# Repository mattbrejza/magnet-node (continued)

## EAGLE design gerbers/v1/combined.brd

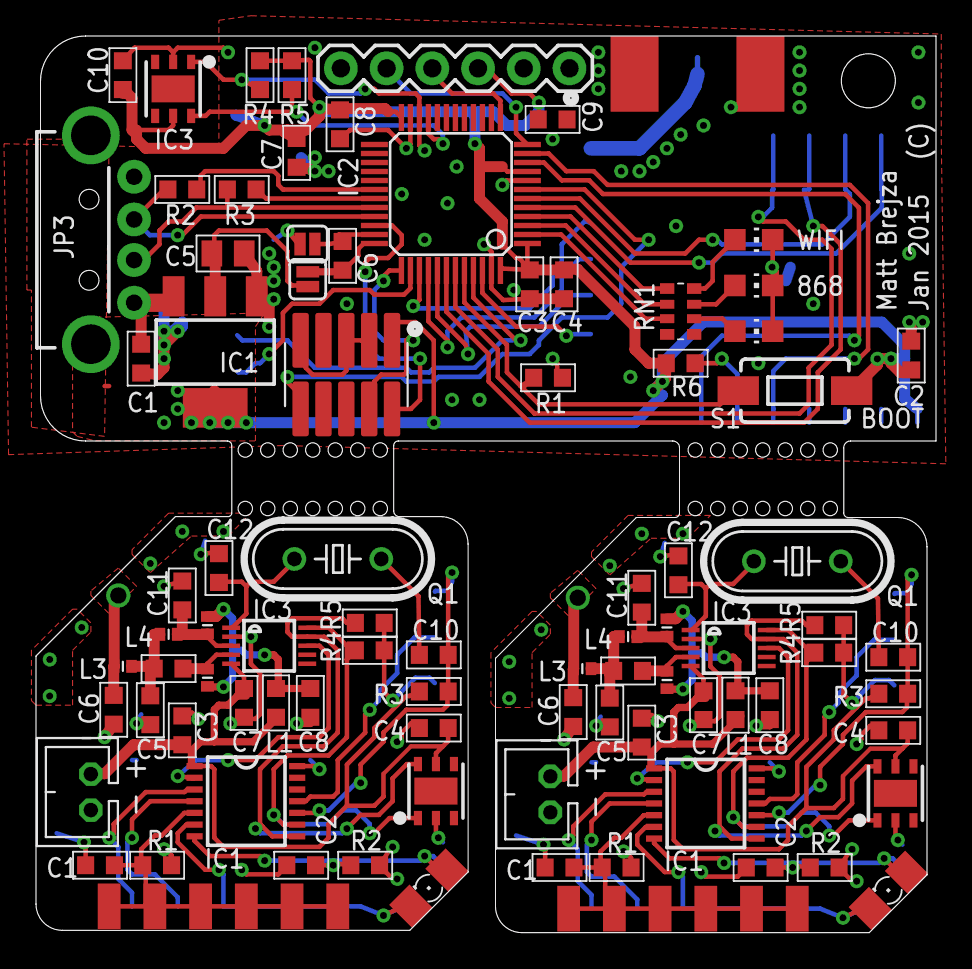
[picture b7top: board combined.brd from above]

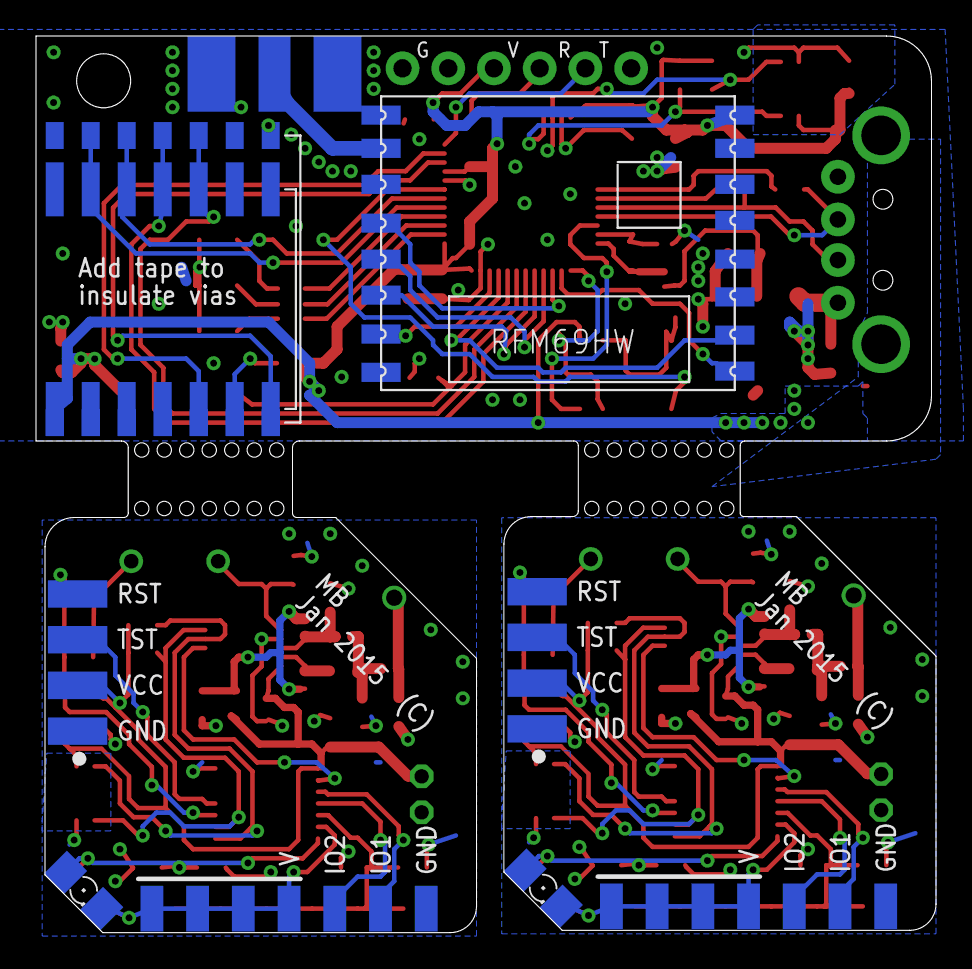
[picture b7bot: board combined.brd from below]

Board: 2 copper layers, 50.0 x 49.8 mm, 97 parts (10 on the bottom side), 76 nets.

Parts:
C1, C2, C3, C13, C22, C23, C26, C27, C28, C29: 100n; C0603-N
C4, C24: C0603-N
C5, C6, C19, C20: 5.1p; C0603-N
C7, C14, C25, C32, C33, C34: 1u; C0603-N
C8, C11, C16, C17: 2.4p; C0603-N
C9, C18: 1.2p; C0603-N
C10, C21: 47n; C0603-N
C12, C15: 14p; C0603-N
C30: 4u7; C0603-N
C31: 4u7; C0805-N
IC1, IC4: MSP430G2X21; TSSOP14
IC2, IC6, IC9: HTU21D; DFN6-L
IC3, IC5: SI4012; MSOP10
IC7: STM32F072; TQFP48
IC8: 1117EMP; SOT223
J1, J2: JST-2-TH
J3: SWD_SHROUD_SMD; SWD_SMD_SHROUD
JP1, JP2: SJ_2S
JP3: USB-A-H
JP4: FTDI_BASICPTH; FTDI_BASIC
L1, L10: 120n; L0603-N
L2, L5, L8, L9: 3.6n; L0402-N
L3, L7: 6.8n; L0402-N
L4, L6: 30n; L0402-N
LED1, LED2, LED3, LED4: 1206
LED5, LED6, LED7: CHIP-LED0805
Q1, Q2: HC49/S
R1, R7: 47k; R0603-N
R2, R6: 1M; R0603-N
R3, R8: 22k; R0603-N
R4, R5, R9, R10, R14, R15: 4k7; R0603-N
R11, R13: 10k; R0603-N
R12: 100k; R0603-N
R16: 1k; R0603-N
RN1: 330; EXB38V
S1: SWITCH-MOMENTARY-2SMD-1101NE; TACTILE-SWITCH-1101NE
SV1, SV3: EDGE_4
SV2, SV4: MA07-1-SMD
U$1, U$2: MA06-1; MA06-1-SMD
U$3: RFM69HW; RFM
U$4: ESP-07
X1: ESP-03
X2: SMA-142-0711-821/826; J502-ND-142-0711-821/826

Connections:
+3V1: C13.1, C14.1, C24.1, IC4.1, IC5.5, IC6.5, J2.1, L10.2, R8.2, R9.2, R10.2, SV1.2
+3V2: C25.1, C27.1, C28.1, C29.1, C31.1, C32.1, C33.1, C34.1, IC7.1, IC7.9, IC7.24, IC7.48, IC8.2, IC8.4, IC9.5, J3.1, JP1.2, JP4.VCC, R14.2, R15.2, R16.1, S1.2, U$3.VCC, U$4.1, X1.1
+3V3: C3.1, C4.1, C7.1, IC1.1, IC2.5, IC3.5, J1.1, L1.2, R3.2, R4.2, R5.2, SV3.2
CH_PD: IC7.5, U$4.13, X1.13
DIO0: IC7.45, U$3.DIO0
DM: IC7.32, JP3.D-, R12.2
DP: IC7.33, JP3.D+, R13.2
GND: C1.1, C2.1, C3.2, C4.2, C5.1, C6.2, C7.2, C8.1, C10.1, C11.1, C12.1, IC1.14, IC2.2, IC3.2, J1.2, Q1.1, R1.1, R2.1, SV2.7, SV3.1
GND1: C13.2, C14.2, C15.1, C16.1, C17.1, C19.1, C20.2, C21.1, C22.1, C23.1, C24.2, IC4.14, IC5.2, IC6.2, J2.2, Q2.1, R6.1, R7.1, SV1.1, SV4.7
GND2: C25.2, C27.2, C28.2, C29.2, C30.2, C31.2, C32.2, C33.2, C34.2, IC7.8, IC7.23, IC7.47, IC8.1, IC9.2, J3.3, J3.5, J3.9, JP2.1, JP3.GND, JP4.GND, LED5.C, LED6.C, LED7.C, R11.1, U$3.GNDA, U$3.GNDB, U$4.8, X1.8, X2.G@1, X2.G@2, X2.G@3, X2.G@4
GPIO0: IC7.10, U$4.7, X1.7
GPIO15: IC7.11, U$4.5, X1.5
I2C2_SCL: IC7.21, IC9.6, R14.1
I2C2_SDA: IC7.22, IC9.1, R15.1
IO1: IC1.3, SV2.6
IO2: IC1.4, SV2.5
IO3: IC4.3, SV4.6
IO4: IC4.4, SV4.5
MISO: IC7.40, U$3.MISO
MOSI: IC7.41, U$3.MOSI
unnamed: IC1.2, IC3.8
unnamed: IC1.11, SV3.3
unnamed: C8.2, L1.1, L2.2, L5.2
unnamed: C12.2, IC3.1, Q1.2
unnamed: IC4.11, SV1.3
unnamed: C5.2, C9.1, L3.1, L4.2
unnamed: C11.2, IC3.3, L4.1, L5.1
unnamed: C9.2, IC3.4, L2.1
unnamed: C6.1, L3.2
unnamed: C15.2, IC5.1, Q2.2
unnamed: C1.2, IC1.5, R1.2, U$1.1, U$1.2, U$1.3, U$1.4, U$1.5, U$1.6
unnamed: C2.2, IC1.7, LED1.A, LED2.A, R2.2
unnamed: C16.2, L8.2, L9.2, L10.1
unnamed: C10.2, IC1.10, R3.1, SV3.4
unnamed: C18.1, C19.2, L6.2, L7.1
unnamed: C17.2, IC5.3, L6.1, L9.1
unnamed: C18.2, IC5.4, L8.1
unnamed: C20.1, L7.2
unnamed: C22.2, IC4.5, R7.2, U$2.1, U$2.2, U$2.3, U$2.4, U$2.5, U$2.6
unnamed: C23.2, IC4.7, LED3.A, LED4.A, R6.2
unnamed: C21.2, IC4.10, R8.1, SV1.4
unnamed: IC4.2, IC5.8
unnamed: C26.1, IC7.36, JP1.1
unnamed: C26.2, IC7.35, JP2.2
unnamed: IC7.44, R11.2, S1.1
unnamed: IC7.31, R12.1
unnamed: IC7.30, R13.1
unnamed: LED5.A, RN1.8
unnamed: LED6.A, RN1.7
unnamed: LED7.A, RN1.6
unnamed: IC7.2, RN1.3
unnamed: IC7.3, RN1.2
unnamed: IC7.4, RN1.1
unnamed: U$3.ANT, X2.1
unnamed: R16.2, U$4.6, X1.6
unnamed: U$4.2, X1.2
unnamed: U$4.4, X1.4
unnamed: U$4.3, X1.3
NRST: IC7.7, J3.10
NSS: IC7.46, U$3.NSS
RST: IC7.38, U$3.RESET
SCK: IC7.39, U$3.SCK
SCL: IC1.8, IC2.6, IC3.9, R5.1
SCL1: IC4.8, IC5.9, IC6.6, R10.1
SDA: IC1.9, IC2.1, IC3.10, R4.1
SDA1: IC4.9, IC5.10, IC6.1, R9.1
SWCLK: IC7.37, J3.4
SWDAT: IC7.34, J3.2
USART1_RX: IC7.43, U$4.10, X1.10
USART1_TX: IC7.42, U$4.11, X1.11
USART2_RX: IC7.13, JP4.TXO
USART2_TX: IC7.12, JP4.RXI
VBUS: C30.1, IC8.3, JP3.VBUS
VCCS: IC1.6, LED1.C, LED2.C, SV2.1, SV2.2, SV2.3, SV2.4
VCCS1: IC4.6, LED3.C, LED4.C, SV4.1, SV4.2, SV4.3, SV4.4
W_RST: IC7.6, U$4.12, X1.12

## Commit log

2014-11-13 started pcb
2014-11-14 initial route
2014-11-14 changing sensor power arragment
2014-11-22 started wifi basestatin
2014-11-23 some routing
2014-11-23 added temp/humid sensor
2014-11-24 moved to smd esp
2014-11-24 something changed probably
2014-11-25 routing improved
2014-11-25 started mppt modelling
2014-11-25 tiding
2014-11-26 started solar node
2014-11-27 added switcher to simulation
2014-12-01 pretty much done
2014-12-01 connector labelljng
2014-12-02 increasing cap package size
2014-12-02 with updated switching stuff
2014-12-08 changed footprints in magnet node
2014-12-18 adding some values and labels
2014-12-18 small changes
2015-01-03 almost done
2015-01-03 routed RST
2015-01-04 removed power control from dht
2015-01-04 almost ready to do
2015-01-05 sent off
2015-01-24 minor changes (i hope)
2015-02-17 adding stencil and couple of values
2015-04-12 started node firmware
2015-04-12 fixing value
2015-04-12 started basestation code
2015-04-12 more basestation tuff
2015-04-12 another file
2015-04-14 added checksum
2015-04-18 adding new breakout
2015-04-20 minor changes
2015-04-27 minor
2015-05-10 minor change
2015-05-30 initial commit of working wifi uplink
2015-05-31 lowered power usage
2015-05-31 wifi fixes
2015-06-22 started wind shield
2015-06-23 turned into assembly
2015-06-24 more 3d stuff
2015-06-30 ui on basestation, adc temp on node
2015-06-30 fixing temp < 0
2015-06-30 can now change wifi network
2015-07-01 improved ui, half way through making wifi nonblocking
2015-07-12 esp stuff is now non blocking
2015-08-07 done some stuff...
2015-08-08 doesnt connect if invalid ssid on startup
2015-08-08 Restructured to include locm3 locally
2015-08-08 Tidying up @mattbrejza's code
2015-08-08 Ignore dependency lists
2015-08-08 Removing shadowed variables and use newlib's _sbrk etc
2015-08-08 More tidying
2015-08-08 removed old locm3
2015-08-08 removed old locm3 mod
2015-08-08 removed old locm3 mod and dir
2015-08-08 Updated locm3 to BuFran's de26102ff6fb5e80afbbc72e0a058746b8cb2272
2015-08-08 Old USB stuff for f0x2
2015-08-08 Working USB roughly, although sometimes fails to enumerate and usbd_poll() isn't run often enough
2015-08-08 Removed a usb write that causes hardfaults
2015-08-10 adding tssop versopn
2015-08-10 some #defines
2015-08-20 Testing a ChibiOS version of the firmware
2015-08-20 getting closer to easy esp programming
2015-08-20 Tidied up board.h to remove artifacts from demo-board-example
2015-08-20 now can flash thru stm32
2015-08-20 Use 'pt boot' or 'pt norm' to enter bootloader or normal passthrough modes on the ESP
2015-08-21 Separated out shell USB stuff
2015-08-21 serusbcfg is not const
2015-08-21 added functionality to allow other threads to get a SDU pointer, so they can chprintf
2015-08-21 typo in comment
2015-08-21 slightly smaller wa is ok for usbserial (for now)
2015-08-21 add semihosting support to allow printf over debug interface
2015-08-22 optionally enable stdio over gdb session
2015-08-23 added light sensor
2015-08-27 some work on the esp
2015-09-01 Updated to ESP thread message format
2015-09-02 RTFM! Objects in mempools must be 32 bit aligned (on stm32)
2015-09-03 working on sending and getting a message from the esp
2015-09-03 Flushes buffers after waiting for the ESP to transmit its stuff after boot
2015-09-03 Once we have a message, process it with all haste!
2015-09-03 We can sleep a little more if the buffer is empty
2015-10-24 reverted to linear buffer
2015-10-24 determining if terminal is attached ???
2015-10-24 receiving and parsing ESP version
2015-10-24 updated chibi
2015-10-24 Working esp version printing over usbser
2015-10-24 Adds functionality to reset the ESP
2015-10-24 added functionality for getting IP
2015-10-24 some improvemets, ap connect isnt blocking
2015-10-24 Can join and examine IP from UI
2015-10-24 Check that ssid and pass are given for a join-AP, otherwise segfault
2015-10-24 ui cleanup
2015-10-24 beginning work on sending http data
2015-10-24 update esp_status struct when the link status and ip status are updated
2015-10-24 working on IP send
2015-10-24 working on IP send 2
2015-10-24 Submitting data to server successfully
2015-10-25 Tidying 2
2015-10-25 calmed things down a bit
2015-10-25 Adding blank thread for RFM processing
2015-10-25 Enable SPI1 and reassign DMA channels
2015-10-25 Set up board.h for using SPI1 for the RFM
2015-10-25 Added syntastic config
2015-10-25 We don't need USART1 because we use the Serial Driver which doesn't use DMA
2015-10-25 Fleshing out SPI interface to RFM
2015-10-25 Setting the rfm mode
2015-10-25 RFM should init but doesn't
2015-10-25 Reset the RFM before attempting init
2015-10-26 Don't remove the message opcode/payload from the mempool until the message has been successfully fulfilled
2015-10-26 Allow setting of node name using > esp setname
2015-10-26 Tidying comments
2015-10-26 Fixed RFM bug causing SS to be asserted/deasserted at the wrong points
2015-10-26 Upped the rfm SPI speed to 1.5MHz
2015-10-26 Added functions to receive from the rfm
2015-10-27 something changed
2015-10-27 added 35mhz tx
2016-01-24 pretty much done tssop version
2016-01-27 almost done 35mhz tranasmitter
2016-01-27 adding some mire testpads
2016-03-13 addin gvalues
2016-03-16 adding sim
2016-03-16 adding ignore file
2016-03-16 updating some ording numbers
2016-03-19 Working RFM sending data to server
2016-03-19 esp thread should post SEND and CLOSE messages ahead of other mailbox items
2016-03-19 Added @adamgreig's threads shell function to show stack sizes and remaining
2016-03-19 firmware for 35mhz tx
2016-03-19 basic operation
2016-03-20 Make sure to set CWMODE=2
2016-03-20 Maintain esp status value so we can see if AP assoc is lost
2016-03-20 Wifi led on when connection active, flickers off when HTTP post in prog
2016-03-20 Renaming
2016-03-20 RFM led on for 500ms when a packet appears
2016-03-20 Use show none|packet|debug to decide what gets printed to shell. none by default
2016-03-20 Just `show` gives the current debug level
2016-03-20 Custom linker script
2016-03-20 Flash storage test ok
2016-03-20 Fixed an infinite wait at a mailbox
2016-03-20 Working flash storage
2016-03-20 Fixes a bug where configuration is read errorneously from the flash
2016-03-20 Added fimrware version
2016-03-20 Longer timeout for esp fails
2016-03-20 Check IP is not 0.0.0.0
2016-03-20 Fixed a bug where content length is wrong causing an overrun on short packets
2016-03-20 Make an rfm_packet which holds the payload and the rssi
2016-03-21 Upload rssi with packets
2016-03-21 Show rssi when show packet enabled
2016-03-22 Fixes flash memory validity settings
2016-03-22 Check we have valid origin and ssid/pass before POSTing
2016-03-23 Closes #3
2016-03-23 Forgot to remove packing
2016-03-23 Upgraded ESP to SDK 1.40/AT 0.50 firmware
2016-03-24 Fixed a bug causing unhandled exception after esp reset
2016-03-24 Always check bufptr from strstr is non-null
2016-03-24 Updated shell command usage message
2016-03-24 Stop rfm and esp threads writing to usbser when ESP-PT enabled
2016-03-24 New esp firmware prints SEND OK instead of UNLINK when HTTP closes
2016-03-24 Fixed a small typo
2016-03-24 Back off rfm polling a tad to reduce rfm_thread cpu usage
2016-03-24 supports spaces in stuff
2016-03-24 re-enabling wdt
2016-03-24 changing flash size to lowest common denominator
2016-03-25 Beginning work on HTU21
2016-03-26 fI2CCLK is 48mhz so set presc=11
2016-03-27 Fixes an unhandled exception caused by multiple responses in the ESP response buffer meaning a buffer overflow was caused when copying the string into user_print_buf
2016-03-28 Adds version reporting and framework for error reporting
2016-03-30 Adds temp/humidity reporting
2016-03-30 2 decimal places for temp, 1 for humidity. Adds HTU timeout handling
2016-04-14 Removes I2C driver from I2C_LOCKED state after a timeout
2017-03-18 Reduced HTTP timeout to stop mailbox overflow on poor network connections
2017-03-18 fixing for new response
2017-03-18 Block read data from the serial buffer (sdReadTimeout) to try and avoid serial buffer overflows, which were previously causing messages to be dropped/aborted since charaecters were dropped from the E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
2017-03-19 1) RFM timeout, reboot if no packets received in a minute. 2) Clear ESP receive buffer only immediately before we send. 3) Check for SEND OK as termination criterion for CIPSEND. 4) 16 mailbox items 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
2017-03-19 Adds age reporting of packets when uploaded, to enable server to time-correct
2017-03-19 Limits number of retries for HTTP POSTs to ESP_RETRIES_MAX
2017-03-19 Fixes a bug where packet age is incorrectly calculated in the HTTP POST requests
2017-03-19 BUG: When mailbox is full, control messages cannot get through to ESP. FIX: if mailbox is full, drop the oldest message.
2017-03-19 CHIBI: Updated to latest stable_3.0.x
2017-03-20 HARDWARE: removes FTDI, HTU21
2017-03-20 HARDWARE: switch to ESP12
2017-03-20 HARDWARE: switch to ESP12 2
